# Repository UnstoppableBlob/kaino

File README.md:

# Kaino (or Kiano)

## What this project is

Here's a short story about this project! I wanted a keyboard from Casio, but it was too expensive for me, so I made my own. I just made a keyboard which should theoretically be able to connect to my computer, and use LMMS that's on my computer, to play sounds that sound exactly like a real piano! 

## How I made it

I made the schematic and PCB in Kicad, which is my prefered software for this type of stuff. I used Shapr3D on my Ipad for the model of the case. I also used Shapr3D's "Visualize" feature for the renders that I got. I plan to use Cherry MX mechanical keyswitches, which are what I have on my pcb renders. I have made my own custom keycap in Shapr3D, which is what I plan to print out and use. Not only does it look like a piano, it feels like one, too. I have put a hole in all of the piano keycaps, and made them a hinge. Whenever you press on a key, it will have the same rotational movement as a really key has. Obviously, I'm limited with the materials of the keycaps that I produce, as I don't have access to the premium ceramic keys that the real pianos have. In addition, even if I did have access to them, the mechanical keyswitches that I'm using wouldn't be able to support the weight of them, at least without substantial springing. My banner image for it is AI Generated, just a disclaimer, hope that it doesn't cause any issues.

## Schematic

## PCB

## Render #1

## Render #2

## Render #3

## Render #4

## BOM
| Item                  | Description              | Quantity           | Unit Price | Total Price | Total (with tax & shipping incl.) | Running Total                                                               | Link                                                                                                                                                                                                                                                                                                                                                                                                                                                                                                                                                                                   |   |   |   |   |                                                                                            |
|-----------------------|--------------------------|--------------------|------------|-------------|-----------------------------------|-----------------------------------------------------------------------------|----------------------------------------------------------------------------------------------------------------------------------------------------------------------------------------------------------------------------------------------------------------------------------------------------------------------------------------------------------------------------------------------------------------------------------------------------------------------------------------------------------------------------------------------------------------------------------------|---|---|---|---|--------------------------------------------------------------------------------------------|
| PCB                   | PCB from jlcpcb          | 5 (jlcpcb minimum) | $0.00      | $0.00       | $0.00                             | $0.00                                                                       | https://cart.jlcpcb.com/quote                                                                                                                                                                                                                                                                                                                                                                                                                                                                                                                                                          |   |   |   |   |                                                                                            |
| Cherry MX switches    | Cherry MX Switches       | 1                  | $0.00      | $0.00       | $0.00                             | $0.00                                                                       | https://www.amazon.com/OUTEMU-Red-Switches-Pin-Switch/dp/B095W1QYPJ/ref=sr_1_10?crid=5KMUPYD6IZAA&dib=eyJ2IjoiMSJ9.ii8hn-4PoCBy9_AF64n2EIdF-8TcQv4n4fZUgrf6eaJl_2E7NqmhJTi7zDvZldSbW1GBUyXt96vEE5SZ91GLxMlmPeL0GdI5OqmHLtCsKP6S4yFXbT0PFL_AmCCw-UflwuoJvqH2WNDOXLrnCfIFiWIC3DsUp4Nng1ZPkXDfcNJ9YehwtTPZZKEcRtRQIGpqlk5xy1gLdXWIZ-g9Wlaw73lw5D9hfxBtmo1eMZbXho8.vcyENYYKR-iks1sqvfSt9besUzxZzQDz3KBChHqnxDw&dib_tag=se&keywords=cherry%2Bmx%2Bswitches%2B5%2Bpin&qid=1777429869&sbo=RZvfv%2F%2FHxDF%2BO5021pAnSA%3D%3D&sprefix=cherry%2Bmx%2Bswitches%2B5%2Bpi%2Caps%2C216&sr=8-10&th=1 |   |   |   |   |                                                                                            |
| Raspberry Pi pico     | MCU                      | NA                 | $0.00      | $0.00       | $0.00                             | $0.00                                                                       | https://www.amazon.com/gp/product/B0C6Q67V97?smid=A1YZW40LYQY3L1&psc=1                                                                                                                                                                                                                                                                                                                                                                                                                                                                                                                 |   |   |   |   | Since I already have plenty of these in my house, I decided to put $0, but included a link |
| 1N4148W (100pcs)      | Diodes                   | 1                  | $0.00      | $0.00       | $0                                | $0.00                                                                       | https://www.aliexpress.us/item/3256807716771073.html?spm=a2g0o.cart.0.0.47a538daYBbt9U&mp=1&pdp_npi=5%40dis%21USD%21USD%201.48%21USD%201.48%21%21USD%201.48%21%21%21%40210328db17669560346357255e1c7d%2112000042781108223%21ct%21US%216953170698%21%211%210&gatewayAdapt=glo2usa                                                                                                                                                                                                                                                                                                       |   |   |   |   |                                                                                            |
| 3D Prints             | 3D printed keys and case | NA                 | $0         | $0          | My own printer                    | $0                                                                          | NA                                                                                                                                                                                                                                                                                                                                                                                                                                                                                                                                                                                     |   |   |   |   |                                                                                            |
| Rotary Encoder (5pcs) | EC11 rotary encoder      | 1                  | $0.00      | $0.00       | $0                                | $0.00                                                                       | https://www.amazon.com/gp/product/B0C6Q67V97?smid=A1YZW40LYQY3L1&psc=1                                                                                                                                                                                                                                                                                                                                                                                                                                                                                                                 |   |   |   |   | I already have some of these lying around from hackpad a long time ago                     |
| Adafruit 1.8 TFT      | LCD Display              | 1                  | $0.00      | $0.00       | $0.00                             | $0.00                                                                       | https://www.adafruit.com/product/358                                                                                                                                                                                                                                                                                                                                                                                                                                                                                                                                                   |   |   |   |   |                                                                                            |
|                |                          |                    |            |             |                                   | Running total is 0 because I'm paying for all costs related to buying parts |                                                                                                                                                                                                                                                                                                                                                                                                                                                                                                                                                                                        |   |   |   |   |                                                                                            |

The total amount of money that I would have to spend would be $72.18, since I'm buying parts myself

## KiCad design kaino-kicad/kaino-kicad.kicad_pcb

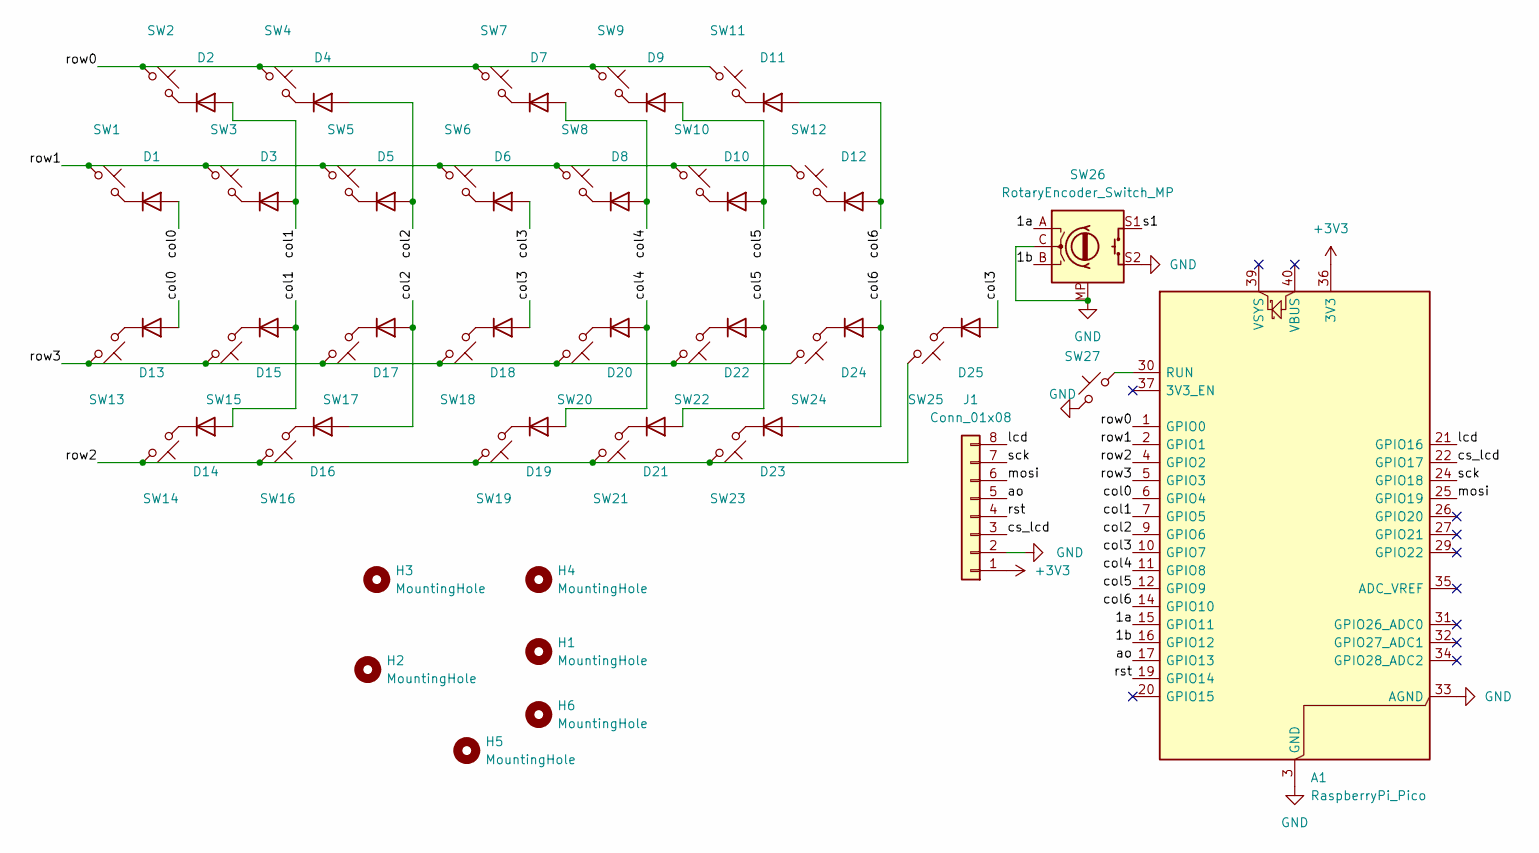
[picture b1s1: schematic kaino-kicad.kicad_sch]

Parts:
A1: RaspberryPi_Pico; RaspberryPi_Pico_Common_Unspecified
D1, D2, D3, D4, D5, D6, D7, D8, D9, D10, D11, D12, D13, D14, D15, D16, D17, D18, D19, D20, D21, D22, D23, D24, D25: 1N4148; D_DO-35_SOD27_P7.62mm_Horizontal
H1, H2, H3, H4, H5, H6: MountingHole; MountingHole_5.3mm_M5
J1: Conn_01x08; PinHeader_1x08_P2.54mm_Vertical
SW1, SW2, SW3, SW4, SW5, SW6, SW7, SW8, SW9, SW10, SW11, SW12, SW13, SW14, SW15, SW16, SW17, SW18, SW19, SW20, SW21, SW22, SW23, SW24, SW25, SW27: SW_Push_45deg; SW_Cherry_MX_1.00u_PCB
SW26: RotaryEncoder_Switch_MP; RotaryEncoder_Alps_EC11E-Switch_Vertical_H20mm_MountingHoles

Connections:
+3V3: A1.36 (3V3), J1.1
/1a: A1.15 (GPIO11), SW26.A
/1b: A1.16 (GPIO12), SW26.B
/ao: A1.17 (GPIO13), J1.5
/col0: A1.6 (GPIO4), D1.2 (A), D13.2 (A)
/col1: A1.7 (GPIO5), D2.2 (A), D3.2 (A), D14.2 (A), D15.2 (A)
/col2: A1.9 (GPIO6), D4.2 (A), D5.2 (A), D16.2 (A), D17.2 (A)
/col3: A1.10 (GPIO7), D6.2 (A), D18.2 (A), D25.2 (A)
/col4: A1.11 (GPIO8), D7.2 (A), D8.2 (A), D19.2 (A), D20.2 (A)
/col5: A1.12 (GPIO9), D9.2 (A), D10.2 (A), D21.2 (A), D22.2 (A)
/col6: A1.14 (GPIO10), D11.2 (A), D12.2 (A), D23.2 (A), D24.2 (A)
/cs_lcd: A1.22 (GPIO17), J1.3
/lcd: A1.21 (GPIO16), J1.8
/mosi: A1.25 (GPIO19), J1.6
/row0: A1.1 (GPIO0), SW2.1, SW4.1, SW7.1, SW9.1, SW11.1
/row1: A1.2 (GPIO1), SW1.1, SW3.1, SW5.1, SW6.1, SW8.1, SW10.1, SW12.1
/row2: A1.4 (GPIO2), SW14.1, SW16.1, SW19.1, SW21.1, SW23.1, SW25.1
/row3: A1.5 (GPIO3), SW13.1, SW15.1, SW17.1, SW18.1, SW20.1, SW22.1, SW24.1
/rst: A1.19 (GPIO14), J1.4
/s1: SW26.S1
/sck: A1.24 (GPIO18), J1.7
GND: A1.3 (GND), A1.8 (GND), A1.13 (GND), A1.18 (GND), A1.23 (GND), A1.28 (GND), A1.33 (AGND), A1.38 (GND), J1.2, SW26.C, SW26.MP, SW26.S2, SW27.2
unnamed: A1.30 (RUN), SW27.1
unnamed: D1.1 (K), SW1.2
unnamed: D2.1 (K), SW2.2
unnamed: D3.1 (K), SW3.2
unnamed: D4.1 (K), SW4.2
unnamed: D5.1 (K), SW5.2
unnamed: D6.1 (K), SW6.2
unnamed: D7.1 (K), SW7.2
unnamed: D8.1 (K), SW8.2
unnamed: D9.1 (K), SW9.2
unnamed: D10.1 (K), SW10.2
unnamed: D11.1 (K), SW11.2
unnamed: D12.1 (K), SW12.2
unnamed: D13.1 (K), SW13.2
unnamed: D14.1 (K), SW14.2
unnamed: D15.1 (K), SW15.2
unnamed: D16.1 (K), SW16.2
unnamed: D17.1 (K), SW17.2
unnamed: D18.1 (K), SW18.2
unnamed: D19.1 (K), SW19.2
unnamed: D20.1 (K), SW20.2
unnamed: D21.1 (K), SW21.2
unnamed: D22.1 (K), SW22.2
unnamed: D23.1 (K), SW23.2
unnamed: D24.1 (K), SW24.2
unnamed: D25.1 (K), SW25.2

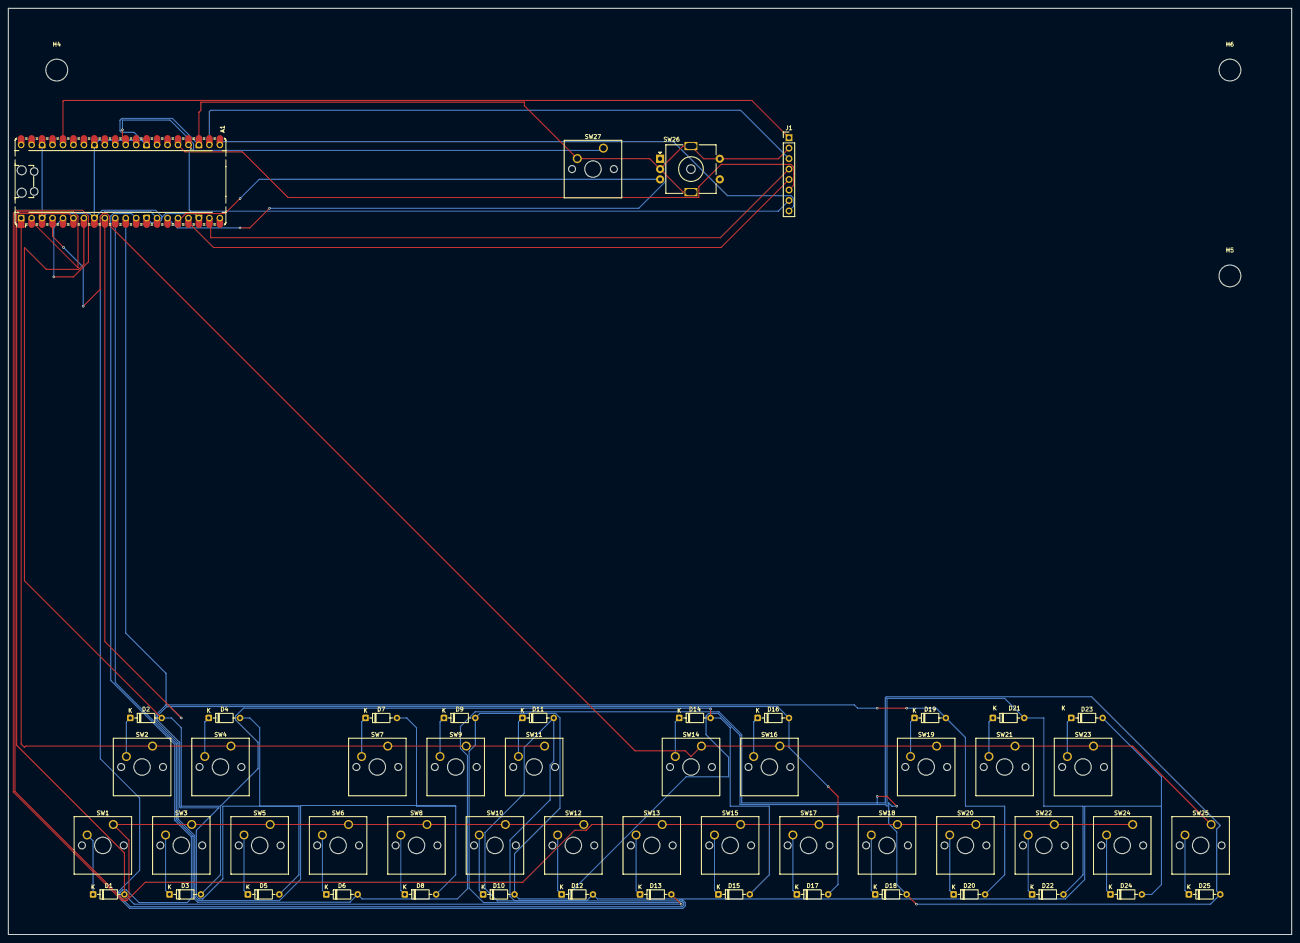
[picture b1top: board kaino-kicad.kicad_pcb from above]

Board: 2 copper layers, 311.8 x 225.0 mm, 57 parts (0 on the bottom side), 47 nets.

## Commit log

2026-04-27 added from old repo
2026-04-27 add images
2026-04-27 added CAD assembly
2026-04-27 organise
2026-04-27 save
2026-04-28 did all the draft firmware, not tested yet
2026-04-28 readme and images
2026-04-29 added bom
2026-04-29 fixed bom
2026-04-29 added case
2026-05-01 added full case
2026-05-04 update readme and bom
